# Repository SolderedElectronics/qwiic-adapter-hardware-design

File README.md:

# qwiic adapter Hardware Design

## About the Product

|  |
| :----------------------------------------------------------: |
| [Buy qwiic adapter](https://www.solde.red/333015) |

Do you have an old I2C board lying around that would be perfect only if it had qwiic connectors? With the qwiic adapter and a little bit of soldering, you can give it new life. It will be able to connect easily to newer boards with qwiic cables.

The adapter has two qwiic connection ports and four plated through-holes: SCL, SDA, 3.3V, and GND. It comes with pins that need to be soldered to the board.

---

## Repository Contents

This repository contains all design files for qwiic adapter, organized as follows:

- **`CAD` folder**: Contains KiCAD design files, including:
  - Schematics
  - PCB layout
  - Panel PCB layout
  - Source 3D files in Fusion360, if any
  - All files are sorted by version with a detailed change log.
- **`OUTPUTS` folder**: Includes all production-ready files, such as:
  - Bill of Materials (BOM) and interactive BOM (iBOM)
  - PDF versions of schematics
  - 3D `.step` file of the board
  - 3D-printable models
  - Gerber files for PCB manufacturing
  - Image of the pinout of the board
  - Product image
  - Compliance, legal and generic sales documents

Refer to the `Change Log` in the CAD folder for details about updates between versions.

---

## Learn More About the Product

Beyond the repository, explore the following resources:

### Soldered Verify

The **Soldered Verify** system ensures every board you purchase from Soldered is fully functional. It also provides access to exclusive test data for your product. To get started, find the unique Soldered Verify ID on your product's packaging and enter the ID on the [Soldered Verify page](https://soldered.com/verify/) to access test results and additional product details.

### Soldered Community

Soldered Community is your go-to place for technical support. Our engineers track and answer all questions posted there, and it’s a great space for the maker community. Get answers to your questions and solutions for your challenges at [Soldered Community](https://soldered.com/community).

### solde.red

solde.red is an ultimate URL shortener and information hub. Access it by typing solde.red/ followed by your product SKU, e.g., [solde.red/333000](https://solde.red/333000), to find getting-started guides, datasheets, open-source hardware and software files, certifications, images, pinouts, and more. Read more about the shortener [here](https://solde.red/info/).

---

## Contributing

Contributions are welcome! Here’s how you can get involved:

- Submit pull requests to enhance the design or fix issues.
- Report bugs or problems by opening an issue.

We encourage community collaboration to make this product even better.

---

## About Soldered

[Soldered for Makers](https://soldered.com) specializes in designing and manufacturing electronic products tailored for enthusiasts, ranging from hobbyists to professionals. Our portfolio includes electronic boards, sensors, and actuators that are widely utilized in fields such as microelectronics, mechatronics, robotics, programming, and IoT. Every product we offer is designed in-house and built upon open-source hardware and software platforms. Proudly certified and manufactured within the European Union, our catalog likely includes the product you need for your project.

We complement these products with comprehensive tutorials and manuals, product descriptions, schematics, programming codes, and project examples. Our round-the-clock [customer and technical support](https://soldered.com/community) is available for all our products, irrespective of the sales channel. Soldered’s success and services reflect our maker community’s unwavering [trust](https://www.trustpilot.com/review/soldered.com), for which we are deeply grateful. Join our community and create using Soldered products.

---

## License

All Soldered open-source hardware (OSH) is under The TAPR Open Hardware License. Read more in the LICENSE file located in this repository.

**Disclaimer:**

No warranty - all designs in this repository are distributed in the hope that they will be useful, but without any warranty. They are provided "AS IS", therefore without warranty of any kind, either expressed or implied. The entire quality and performance of what you do with the contents of this repository are your responsibility. In no event Soldered Electronics will be liable for your damages, or losses, including any general, special, incidental, or consequential damage arising out of the use or inability to use the contents of this repository. 

---

## Have fun!

Thank you for your support from your fellow makers at Soldered Electronics.

Happy Making!

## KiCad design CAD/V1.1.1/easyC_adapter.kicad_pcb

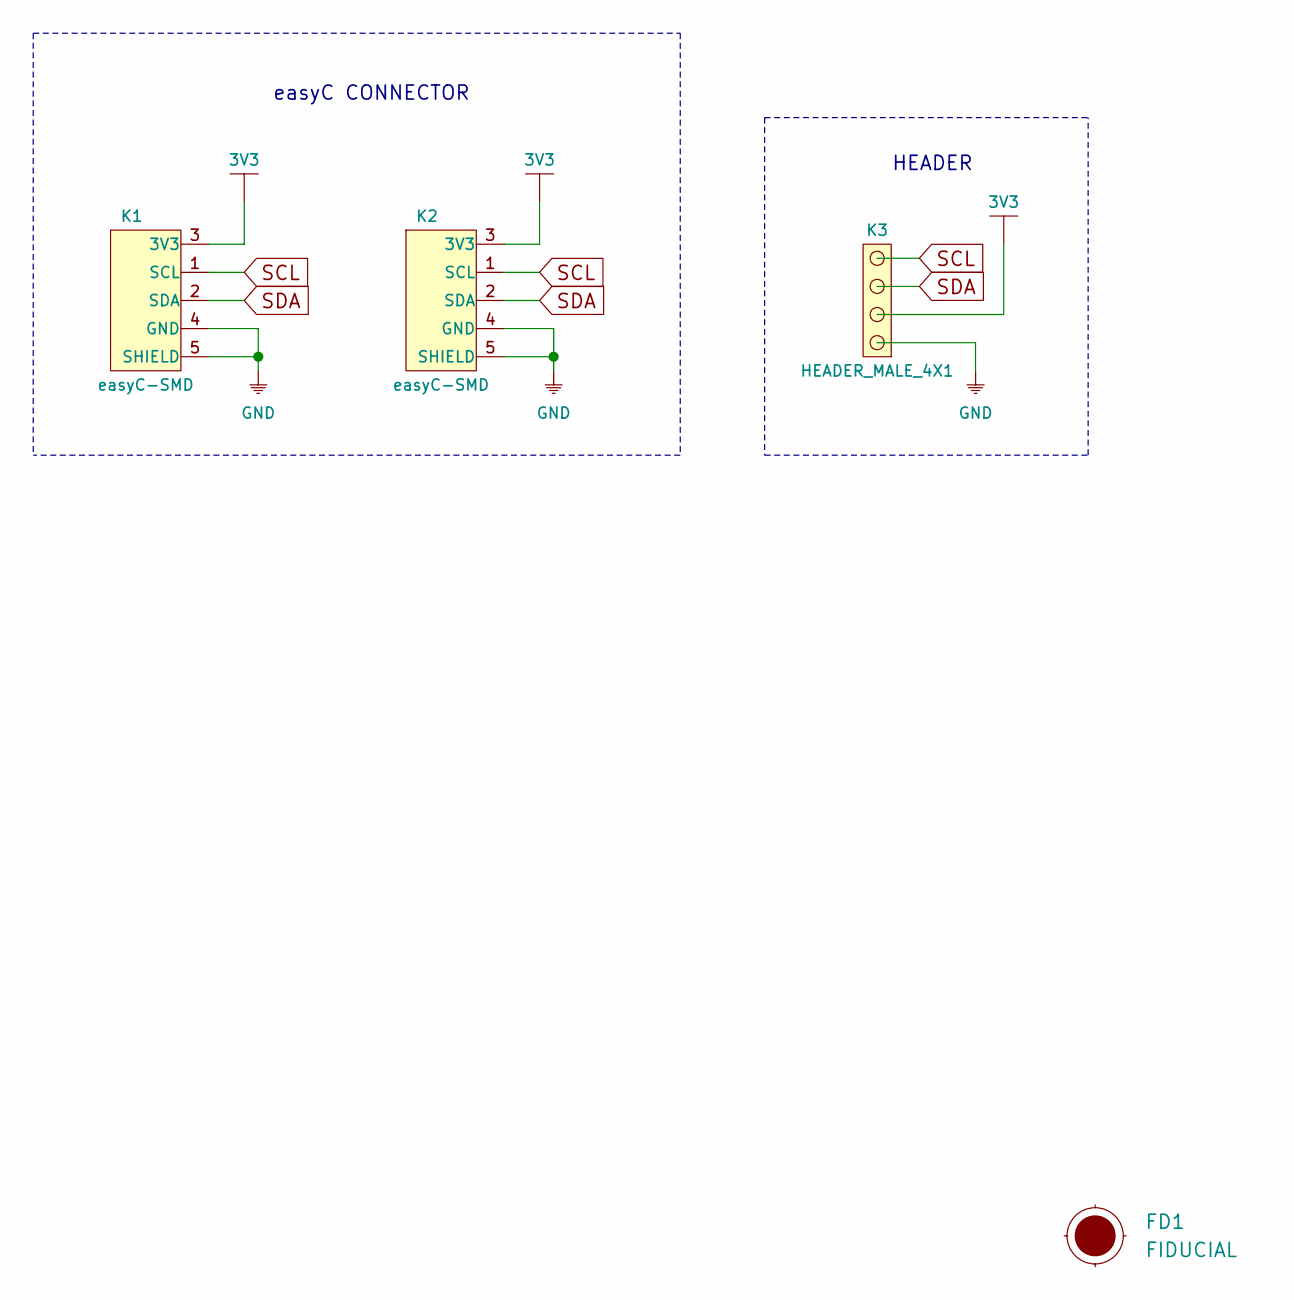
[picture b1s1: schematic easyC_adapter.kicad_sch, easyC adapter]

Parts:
FD1: FIDUCIAL; FIDUCIAL_23
K1, K2: easyC-SMD; easyC-connector
K3: HEADER_MALE_4X1

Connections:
3V3: K1.3 (3V3), K2.3 (3V3), K3.2
GND: K1.4 (GND), K1.5 (SHIELD), K2.4 (GND), K2.5 (SHIELD), K3.1
SCL: K1.1 (SCL), K2.1 (SCL), K3.4
SDA: K1.2 (SDA), K2.2 (SDA), K3.3

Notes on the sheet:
easyC CONNECTOR
HEADER

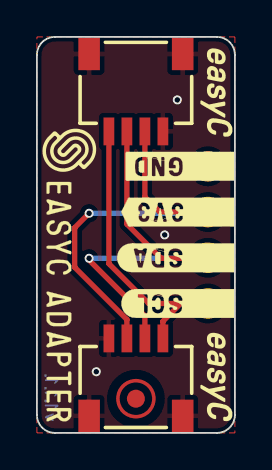
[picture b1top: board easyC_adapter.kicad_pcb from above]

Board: 2 copper layers, 11.0 x 22.0 mm, 4 parts (1 on the bottom side), 4 nets.

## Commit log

2022-08-06 Updating open source files.
